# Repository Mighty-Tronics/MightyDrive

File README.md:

# MT Drive — Four-Channel PWM Pump Interface

**Certified Open Source Hardware — [OSHWA LU000003](https://certification.oshwa.org/lu000003.html)**

MT Drive is an open-hardware power interface for controlling up to four brushed DC pumps or comparable inductive DC loads from an external microcontroller.

Each channel accepts an independent PWM command and switches the load through a protected low-side MOSFET stage. The microcontroller, firmware, regulated +5 V logic supply, motor supply and pumps remain external to the board.

> **Hardware status:** prototype revision V2.0, manufactured by JLCPCB and under qualification.  
> **Published electrical rating:** 2 A continuous per channel, 8 A continuous total.  
> **Extended operation:** up to 3 A per channel may be characterized, but is not guaranteed for this hardware revision.

## Main specifications

| Characteristic | Published specification |
| --- | --- |
| Number of channels | 4 independent outputs |
| Motor supply | 5–36 V DC, externally supplied |
| Continuous current | 2 A maximum per channel |
| Aggregate continuous current | 8 A maximum |
| Extended characterization | Up to 3 A per channel / 12 A total, not guaranteed |
| PWM frequency | 31.5 kHz nominal |
| PWM input levels | 3.3 V or 5 V logic |
| Logic supply | Regulated +5 V external supply |
| Switching topology | N-channel MOSFET, low-side switching |
| Intended ambient range | −10 °C to +50 °C |
| Galvanic isolation | None; logic and motor power use a common ground |
| Hardware reference | Pump Interface schematic V2.0, dated 24 April 2026 |

At 36 V and the published current rating, the board can deliver up to 72 W per load and 288 W to four loads. These values are load power, not PCB dissipation.

## Functional operation

### Power entry

The motor supply enters through `J1`:

- `PWR`: positive motor supply, 5–36 V DC;
- `GND`: common power and logic reference.

The common input stage includes:

- `D5` 15SQ100 series Schottky diode for reverse-polarity protection;
- `D6` 1.5KE43A TVS diode for supply transient suppression;
- `C1` 1000 µF, `C2` 10 µF and `C3` 100 nF for rail decoupling;
- `TP1` and `TP2` for protected `Vin+` and ground measurements.

### PWM command path

Each PWM input passes through a 1 kΩ series resistor and a 100 kΩ pull-down before entering one section of the `74AHCT125` buffer. The buffer is powered from +5 V and adapts a 3.3 V or 5 V controller signal to the 5 V MOSFET gate-control network.

The `74AHCT125` has been bench-tested for this level-adaptation function. It carries gate-drive current only and does not determine the motor-current rating.

The four buffer outputs are permanently enabled because their active-low `/OE` inputs are tied to ground. Gate pull-down resistors keep the MOSFETs off when the controller is disconnected or its outputs are high-impedance.

### Load switching

When a PWM command is high, the corresponding `IRLZ44N` MOSFET turns on. Current flows from `Vin+`, through the channel PTC, through the external load connected between `Mx+` and `Mx−`, and through the MOSFET to ground.

When the MOSFET turns off, the channel flyback diode maintains a local path for the inductive load current. A 22 Ω + 1 nF series RC snubber damps high-frequency ringing across each motor output.

## Connections

### J2 — Logic and PWM

| Pin | Signal | Description |
| ---: | --- | --- |
| 1 | +5 V | External regulated logic supply |
| 2 | GND | Common controller and power-stage reference |
| 3 | PWM1 | Channel 1 command |
| 4 | PWM2 | Channel 2 command |
| 5 | PWM3 | Channel 3 command |
| 6 | PWM4 | Channel 4 command |

### J3 — Pump outputs

| Pin | Signal | Pin | Signal |
| ---: | --- | ---: | --- |
| 1 | M3+ | 2 | M3− |
| 3 | M4+ | 4 | M4− |
| 5 | M2+ | 6 | M2− |
| 7 | M1+ | 8 | M1− |

### Test points

| Test point | Signal |
| --- | --- |
| TP1 | Protected motor rail `Vin+` |
| TP2 | GND |
| TP3 | Channel 1 gate, `Qg1` |
| TP10 | Channel 2 gate, `Qg2` |
| TP11 | Channel 3 gate, `Qg3` |
| TP12 | Channel 4 gate, `Qg4` |

## Protection and reliability architecture

Each channel contains:

- one `MF-R500` resettable PTC in the positive load feed;
- one `15SQ100` flyback diode;
- local 22 µF + 100 nF supply decoupling;
- one 22 Ω / 0.5 W + 1 nF series RC snubber;
- a 10 kΩ MOSFET gate pull-down;
- a 1N4148 gate clamp and gate-conditioning capacitors.

The protections have different roles and do not replace one another. The PTC limits sustained fault energy but is not a precision current limiter. The flyback diode controls inductive current, the snubber damps local ringing, and the TVS limits disturbances reaching the common supply rail.

The 55 V `IRLZ44N` has 19 V of absolute drain-voltage headroom at a 36 V supply. The internal qualification target is a repetitive `VDS` peak no greater than 45 V under the published load, worst switching condition and longest intended motor cable.

## Current and thermal basis

The 2 A/channel rating is based on the complete current path rather than on the headline rating of a single semiconductor.

- Four channels at 2 A give an 8 A continuous common-path current.
- Using the 15SQ100 maximum forward-voltage screening value of 0.82 V gives a conservative `D5` loss bound of 6.56 W at 8 A. Actual forward drop and case temperature must be measured.
- The `MF-R500` hold current falls with ambient temperature; 2 A retains useful margin up to the declared +50 °C design ambient.
- MOSFET conduction and switching losses are verified at 31.5 kHz from measured gate and drain waveforms.
- Power-component case temperatures are checked against the 90 °C internal qualification target.

Operation above 2 A per channel, up to 3 A, is an engineering-characterization region only. It depends on duty cycle, pump start and stall current, ambient temperature, airflow, wiring, connector losses and simultaneous channel loading.

## Integration requirements

1. Connect the controller ground to `J2 GND` before applying PWM signals.
2. Apply a regulated +5 V supply to `J2`; the board does not generate this voltage.
3. Use a current-limited motor supply for first power-up.
4. Size the supply, connectors and cable loop for 8 A continuous total current plus pump start-current transients.
5. Keep PWM and ground wiring short and route motor cables away from sensitive logic wiring.
6. Do not exceed 2 A continuous on any channel or 8 A continuous in total within the published specification.
7. Verify each pump's start and stall current before qualification in the final system.

The board does not regulate motor voltage, provide active electronic current limiting or provide galvanic isolation. It is a component for integration, not a complete protected end product.

## Validation plan

The production-representative board is verified using the following sequence:

1. Inspect component orientation, solder joints and unpowered resistance paths.
2. Apply logic power only and verify all four PWM inputs, buffer outputs and MOSFET gates at 3.3 V and 5 V input levels.
3. Test each channel with a current-limited resistive load before connecting pumps.
4. Verify operation at 31.5 kHz and 10%, 50% and 90% duty cycle.
5. Qualify one channel at 36 V / 2 A over the full duty-cycle range.
6. Qualify four simultaneous channels at 36 V / 2 A per channel after thermal stabilization.
7. Measure MOSFET `VDS` peaks and ringing with the longest intended cable.
8. Record start, stall, reverse-polarity, endurance and high-ambient behaviour.
9. Characterize operation progressively above 2 A and up to 3 A separately, without changing the published rating.
10. Complete EMC pre-compliance tests using the final PCB, pumps, supply and cabling.

No CE conformity claim is made solely from this prototype or this repository. Regulatory assessment applies to the final integrated product and its intended use.

## Repository contents

The repository separates editable design sources from documentation and generated manufacturing outputs:

| Location | Contents |
| --- | --- |
| `Documentation/` | BOM in ODS and CSV formats; schematic images; drill maps; Gerber and Excellon manufacturing files in a ZIP archive; Master Drawing; functional and engineering notes. |
| `Kicad_Files/` | Native KiCad files for viewing and editing the schematic and PCB. |
| `README.md` | Project overview, specifications, integration guidance and certification information. |
| `LICENSE.md` | Project licence information. |

The native KiCad files are the authoritative editable design sources. Rendered schematics, PDFs and manufacturing files are provided for convenient review and production, but do not replace the native source files.

Every hardware release must identify its PCB revision or release date and match it to an immutable repository tag, BOM, schematic, layout and validation evidence.

[Master Drawing — Pump Interface, Rev A](https://github.com/Mighty-Tronics/MightyDrive/blob/main/Documentation/Pump_Interface_MasterDrawing_Rev_A.pdf)

## OSHWA certification

**MT Drive is certified open source hardware under the Open Source Hardware Association (OSHWA) certification program.** The project is registered as **Mighty Drive** in the official OSHWA directory.

| Certification information | Details |
| --- | --- |
| Registered project name | Mighty Drive |
| Unique identifier (UID) | **LU000003** |
| Certification date | **3 October 2026** |
| Official registration | [OSHWA project record — LU000003](https://certification.oshwa.org/lu000003.html) |

OSHWA certification identifies projects that comply with the [Open Source Hardware Definition](https://oshwa.org/definition/). The editable design files and project documentation are published so that users can study, modify, build and distribute the design under the applicable licence.

**Certification scope:** OSHWA certification concerns open-source hardware compliance. It does not certify electrical performance, product safety or CE/EMC conformity. Hardware qualification and final-system regulatory assessment are addressed separately in the validation plan above.

The certification mark and UID refer to the project covered by the official registration. Use of the mark follows the [OSHWA Certification Mark Usage Guidelines](https://certification.oshwa.org/mark-usage.html).

## License

The hardware design and original project documentation are released under the **CERN Open Hardware Licence Version 2 — Strongly Reciprocal (`CERN-OHL-S-2.0`)**. See [`LICENSE.md`](LICENSE.md) and the [official CERN-OHL-S v2 licence text](https://ohwr.org/cern_ohl_s_v2.txt) for the applicable terms.

| Project material | License |
| --- | --- |
| Hardware design, schematic, PCB, fabrication files and BOM | CERN-OHL-S-2.0 |
| Original project documentation | CERN-OHL-S-2.0 |
| Software or firmware | None included in this release |

Third-party data sheets and manufacturer files retain their owners' respective rights and are not relicensed by their inclusion or citation. The OSHWA certification mark remains subject to OSHWA's own usage terms.

## Documentation

The detailed functional description, engineering calculations, component-level implementation and qualification criteria are provided in the project documentation under [`Documentation/`](Documentation/).

## Maintainer

[info@mightytronics.eu](mailto:info@mightytronics.eu)

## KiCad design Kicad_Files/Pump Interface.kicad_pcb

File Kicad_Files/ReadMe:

This folder include all schematics and pcb files done by Kicad 10.

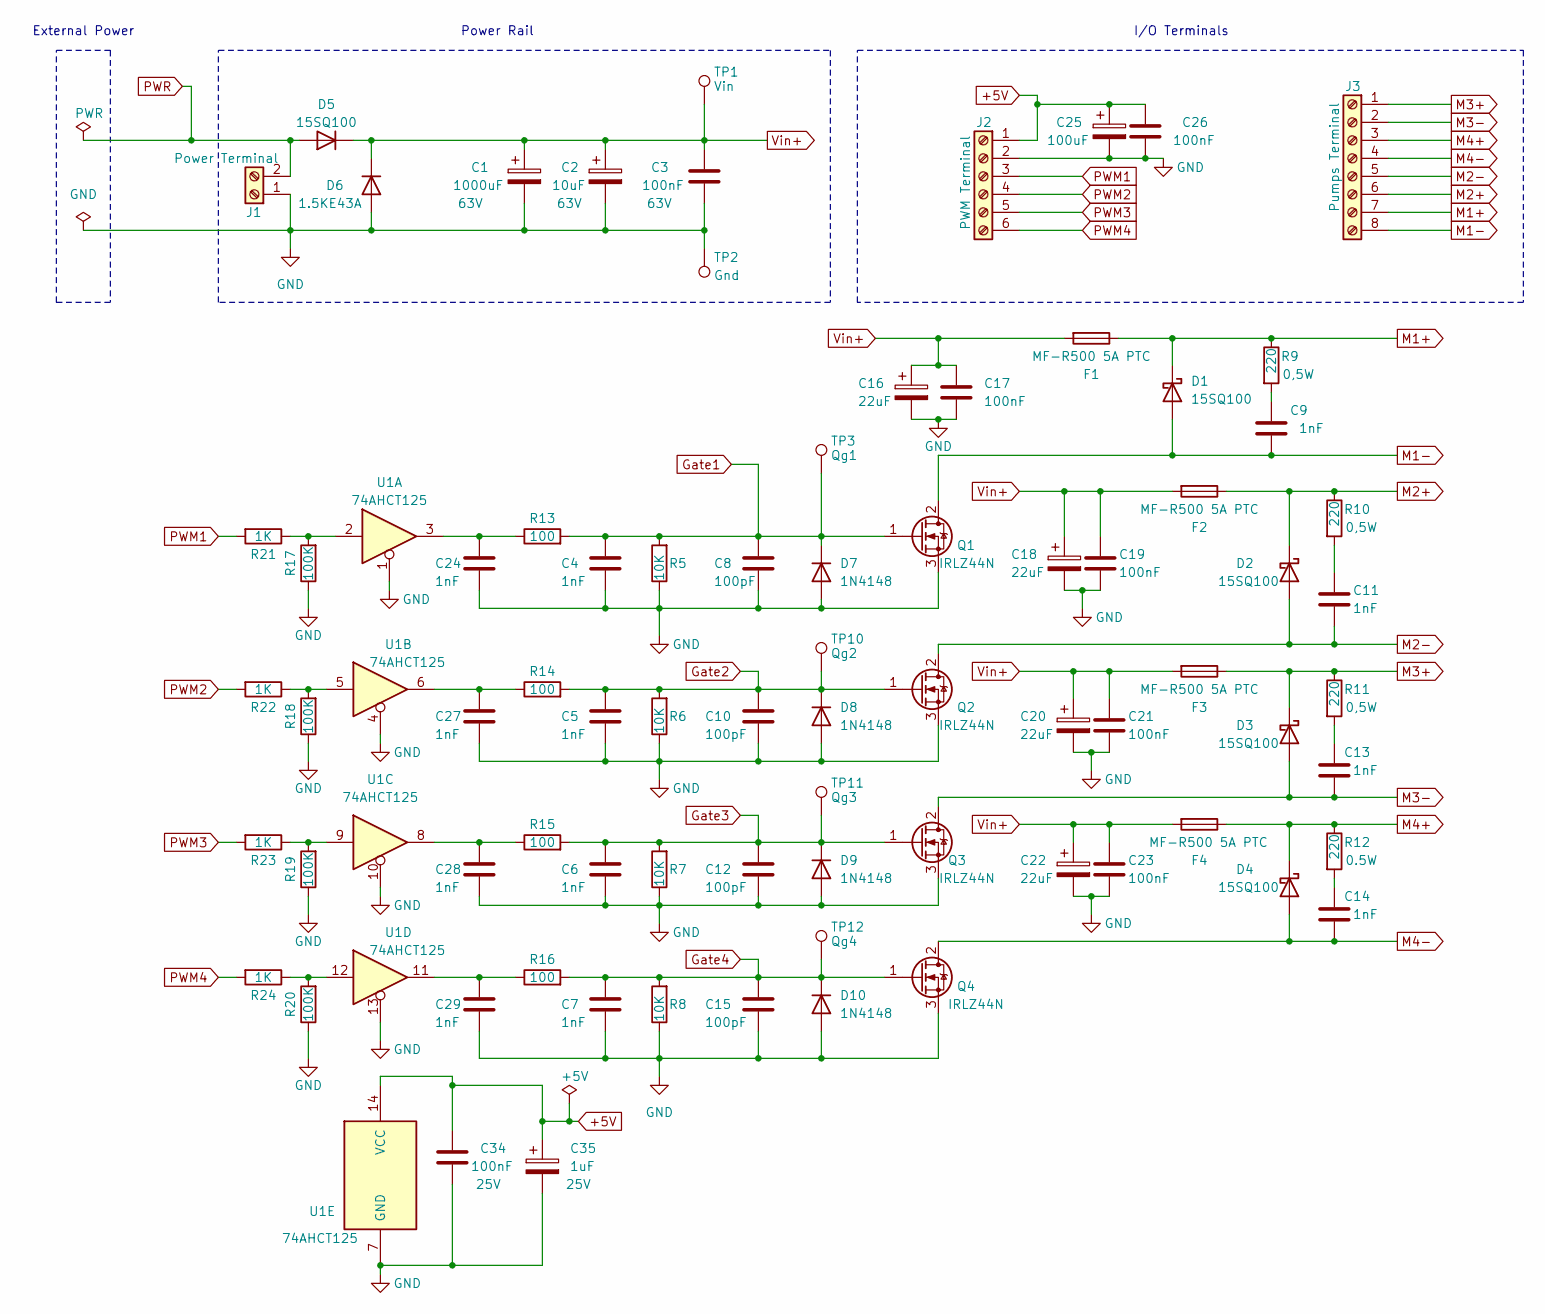
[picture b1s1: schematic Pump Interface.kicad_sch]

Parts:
C1: 1000uF; CP_Radial_D12.5mm_P5.00mm
C2: 10uF; CP_Radial_D6.3mm_P2.50mm
C3, C17, C19, C21, C23, C26: 100nF; C_Disc_D5.0mm_W2.5mm_P5.00mm
C4, C5, C6, C7, C24, C27, C28, C29: 1nF; C_Disc_D5.0mm_W2.5mm_P5.00mm
C8, C10, C12, C15: 100pF; C_Disc_D3.4mm_W2.1mm_P2.50mm
C9, C11, C13, C14: 1nF; C_Rect_L7.2mm_W2.5mm_P5.00mm_FKS2_FKP2_MKS2_MKP2
C16, C18, C20, C22: 22uF; CP_Radial_D6.3mm_P2.50mm
C25: 100uF; CP_Radial_D6.3mm_P2.50mm
C34: 100nF; C_0805_2012Metric
C35: 1uF; C_0805_2012Metric
D1, D2, D3, D4, D5: 15SQ100; D_DO-201AD_P15.24mm_Horizontal
D6: 1.5KE43A; D_DO-201AD_P15.24mm_Horizontal
D7, D8, D9, D10: 1N4148; D_DO-35_SOD27_P7.62mm_Horizontal
F1, F2, F3, F4: MF-R500 5A PTC; Fuse_Littelfuse-LVR100
J1: Power Terminal; TerminalBlock_Phoenix_MKDS-1,5-2-5.08_1x02_P5.08mm_Horizont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
J2: PWM Terminal; TerminalBlock_WAGO_233-506_2x06_P2.54mm
J3: Pumps Terminal; TerminalBlock_Phoenix_MKDS-1,5-8-5.08_1x08_P5.08mm_Horizont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
Q1, Q2, Q3, Q4: IRLZ44N; TO-220-3_Vertical
R5, R6, R7, R8: 10K; R_Axial_DIN0207_L6.3mm_D2.5mm_P10.16mm_Horizontal
R9, R10, R11, R12: 220; R_Axial_DIN0411_L9.9mm_D3.6mm_P12.70mm_Horizontal
R13, R14, R15, R16: 100; R_Axial_DIN0207_L6.3mm_D2.5mm_P10.16mm_Horizontal
R17, R18, R19, R20: 100K; R_Axial_DIN0207_L6.3mm_D2.5mm_P10.16mm_Horizontal
R21, R22, R23, R24: 1K; R_Axial_DIN0207_L6.3mm_D2.5mm_P10.16mm_Horizontal
TP1: Vin; TestPoint_Pad_1.5x1.5mm
TP2: Gnd; TestPoint_Pad_1.5x1.5mm
TP3: Qg1; TestPoint_Pad_1.5x1.5mm
TP10: Qg2; TestPoint_Pad_1.5x1.5mm
TP11: Qg3; TestPoint_Pad_1.5x1.5mm
TP12: Qg4; TestPoint_Pad_1.5x1.5mm
U1: 74AHCT125; SOIC-14_3.9x8.7mm_P1.27mm

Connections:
+5V: C25.1, C26.2, C34.2, C35.1, J2.1, U1.14 (VCC)
GND: C1.2, C2.2, C3.1, C4.1, C5.1, C6.1, C7.1, C8.1, C10.1, C12.1, C15.1, C16.2, C17.2, C18.2, C19.2, C20.2, C21.2, C22.2, C23.2, C24.1, C25.2, C26.1, C27.1, C28.1, C29.1, C34.1, C35.2, D6.2 (A), D7.2 (A), D8.2 (A), D9.2 (A), D10.2 (A), J1.1, J2.2, Q1.3 (S), Q2.3 (S), Q3.3 (S), Q4.3 (S), R5.1, R6.1, R7.1, R8.1, R17.1, R18.1, R19.1, R20.1, TP2.1 (1_1), U1.1, U1.4, U1.7 (GND), U1.10, U1.13
Gate1: C4.2, C8.2, D7.1 (K), Q1.1 (G), R5.2, R13.2, TP3.1 (1_1)
Gate2: C5.2, C10.2, D8.1 (K), Q2.1 (G), R6.2, R14.2, TP10.1 (1_1)
Gate3: C6.2, C12.2, D9.1 (K), Q3.1 (G), R7.2, R15.2, TP11.1 (1_1)
Gate4: C7.2, C15.2, D10.1 (K), Q4.1 (G), R8.2, R16.2, TP12.1 (1_1)
M1+: D1.1 (K), F1.1, J3.7, R9.1
M1-: C9.2, D1.2 (A), J3.8, Q1.2 (D)
M2+: D2.1 (K), F2.1, J3.6, R10.1
M2-: C11.2, D2.2 (A), J3.5, Q2.2 (D)
M3+: D3.1 (K), F3.1, J3.1, R11.1
M3-: C13.2, D3.2 (A), J3.2, Q3.2 (D)
M4+: D4.1 (K), F4.1, J3.3, R12.1
M4-: C14.2, D4.2 (A), J3.4, Q4.2 (D)
unnamed: C9.1, R9.2
unnamed: C11.1, R10.2
unnamed: C13.1, R11.2
unnamed: C14.1, R12.2
unnamed: C24.2, R13.1, U1.3
unnamed: C27.2, R14.1, U1.6
unnamed: C28.2, R15.1, U1.8
unnamed: C29.2, R16.1, U1.11
unnamed: R17.2, R21.1, U1.2
unnamed: R18.2, R22.1, U1.5
unnamed: R19.2, R23.1, U1.9
unnamed: R20.2, R24.1, U1.12
PWM1: J2.3, R21.2
PWM2: J2.4, R22.2
PWM3: J2.5, R23.2
PWM4: J2.6, R24.2
PWR: D5.2 (A), J1.2
Vin+: C1.1, C2.1, C3.2, C16.1, C17.1, C18.1, C19.1, C20.1, C21.1, C22.1, C23.1, D5.1 (K), D6.1 (K), F1.2, F2.2, F3.2, F4.2, TP1.1 (1_1)

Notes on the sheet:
I/O Terminals
External Power
Power Rail

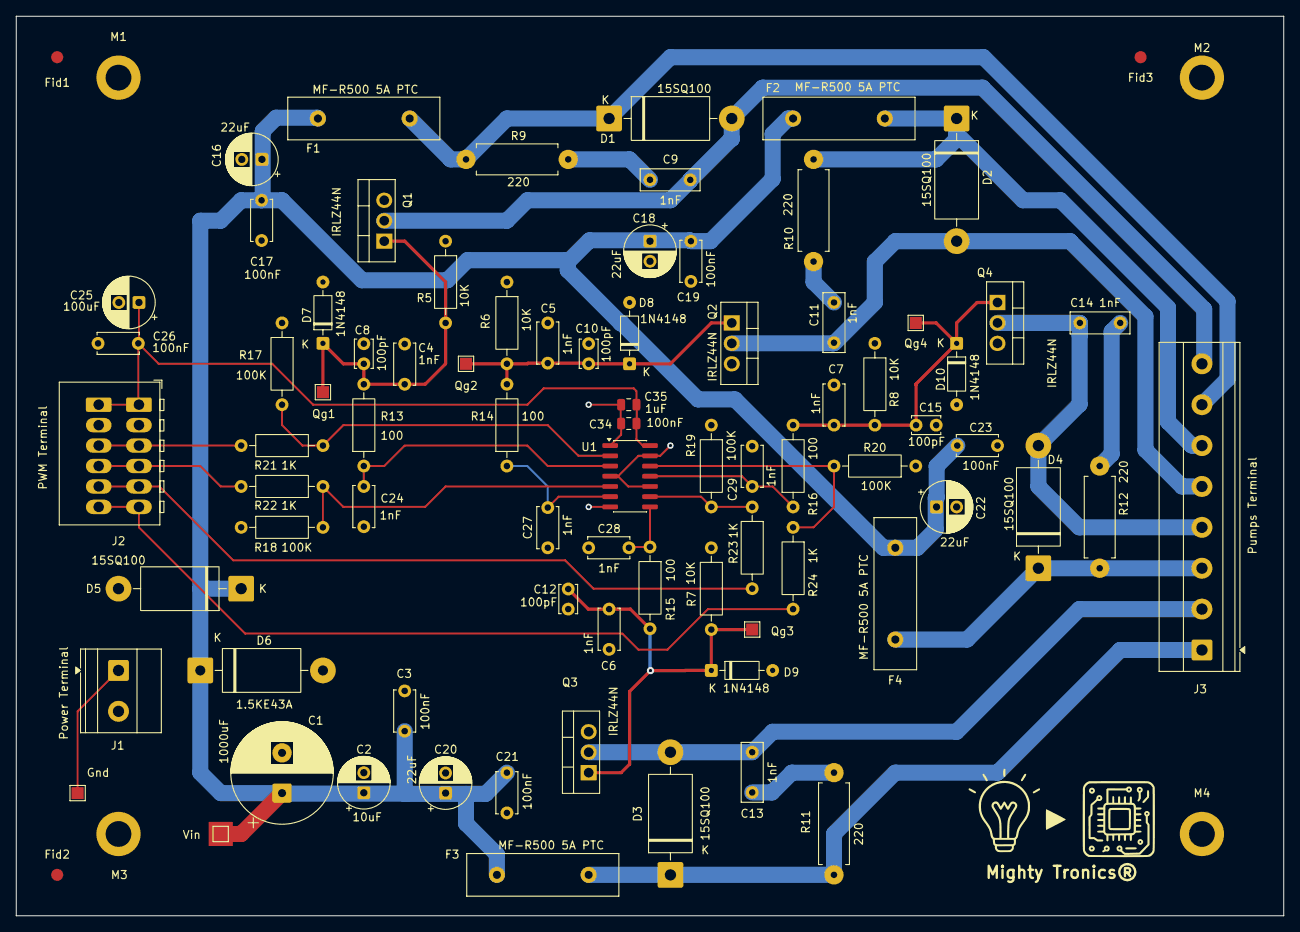
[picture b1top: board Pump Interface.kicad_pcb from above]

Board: 4 copper layers, 157.5 x 111.8 mm, 87 parts (0 on the bottom side), 32 nets.

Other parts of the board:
Fid1, Fid2, Fid3: Fiducial_1.5mm_Mask3mm
M1, M2, M3, M4: MountingHole_3.2mm_M3_ISO14580_Pad
Mighty Tronics®: LOGO; Logo-MT-PCB

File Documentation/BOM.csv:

,,,,,,,,,,,,,,
"MTDrive  bill of materials, schematic V2.0",,,,,,,,,,,,,,
"All components THT except U1, C34 and C35. Suggested footprints require PCB confirmation.",,,,,,,,,,,,,,
,,,,,,,,,,,,,,
References,Qty,Value,Function / location,Technology / specification,Mount,Package / footprint to confirm,Voltage rating (V),Power rating (W),Manufacturer P/N,Supplier P/N,Status / engineering check,,Review priorities,
C1,1,1000 uF,Main DC bus,"Aluminium electrolytic, ripple/ESR specified",THT,Radial; size and pitch TBD,100,,,,Existing 63 V marking to revise; verify surge and physical fit,,D5,Thermal dissipation in 12 A common input
C2,1,10 uF,Main DC bus,Aluminium electrolytic,THT,Radial; size and pitch TBD,100,,,,Existing 63 V marking to revise,,R9-R12,220 ohm in supplied schematic; confirm actual build
C3,1,100 nF,Main DC bus,Ceramic X7R; effective capacitance at 36 V,THT,Radial disc; pitch TBD,100,,,,Existing 63 V marking to revise,,U1,74AHCT125 versus 74HCT125 identification
C4-C7,4,1 nF,Gate network,Ceramic C0G/NP0,THT,Radial disc; pitch TBD,50,,,,Confirm exact gate-source voltage,,PCB,Verify all proposed footprints and motor switching nets
"C8,C10,C12,C15",4,100 pF,Gate network,Ceramic C0G/NP0,THT,Radial disc; pitch TBD,50,,,,,,,
"C9,C11,C13,C14",4,1 nF,Motor snubbers,Pulse-rated polypropylene film,THT,Radial film; pitch TBD,160,,,,160 V provisional; check measured transient and pulse rating,,,
"C16,C18,C20,C22",4,22 uF,Channel bus,Aluminium electrolytic; ripple/ESR specified,THT,Radial; size and pitch TBD,100,,,,,,,
"C17,C19,C21,C23",4,100 nF,Channel bus,Ceramic X7R; DC bias checked,THT,Radial disc; pitch TBD,100,,,,,,,
"C24,C27-C29",4,1 nF,Buffer output filter,Ceramic C0G/NP0,THT,Radial disc; pitch TBD,50,,,,Only buffer supply capacitors C34/C35 are SMD,,,
C25,1,100 uF,5 V input,Aluminium electrolytic,THT,Radial; size and pitch TBD,16,,,,,,,
C26,1,100 nF,5 V input,Ceramic X7R,THT,Radial disc; pitch TBD,25,,,,,,,
C34,1,100 nF,U1 local 5 V decoupling,Ceramic X7R,SMD,0805 candidate; verify PCB,25,,,,One of the two SMD capacitors,,,
C35,1,1 uF,U1 local 5 V decoupling,Ceramic X7R; DC bias checked,SMD,0805/1206 candidate; verify PCB,25,,,,One of the two SMD capacitors,,,
D1-D4,4,15SQ100,Per-channel freewheel diode,"Schottky, 100 V / 15 A nominal; thermal check",THT,R-6 axial; verify exact vendor,,,,,Datasheet link in screenshot points to unrelated 1N5817,,,
D5,1,15SQ100,Series input polarity diode,"Schottky, 100 V / 15 A nominal; thermal check at 12 A",THT,R-6 axial; verify exact vendor,,,,,Critical thermal review of common 12 A path,,,
D6,1,1.5KE43A,Supply TVS,Unidirectional TVS; verify polarity and surge energy,THT,DO-201 axial candidate; confirm vendor,,,,,Check clamp voltage against all bus parts,,,
D7-D10,4,1N4148,Gate clamp network,Small-signal switching diode,THT,DO-35 axial,,,,,Check orientation and forward-current pulses,,,
F1-F4,4,MF-R500 5A PTC,Per-channel resettable protection,PTC hold/trip current at operating temperature,THT,Radial PTC; pitch TBD,,,,,Verify I_hold at 50 C for 3 A and startup trip behavior,,,
J1,1,Power Terminal,Pump supply input,Terminal block; >=12 A continuous plus margin,THT,Pitch and footprint TBD,,,,,Check total current and cable gauge,,,
J2,1,PWM Terminal,Logic supply and 4 PWM inputs,Terminal block; pinout and pitch TBD,THT,Pitch and footprint TBD,,,,,,,,
J3,1,Pumps Terminal,Four motor outputs,Terminal block; >=3 A each plus margin,THT,Pitch and footprint TBD,,,,,Check each contact rating,,,
Q1-Q4,4,IRLZ44N,Four switching MOSFETs,Logic-level N-channel; hot R_DS(on)/SOA check,THT,TO-220-3; verify PCB orientation,,,,,Confirm pin mapping and net topology before power testing,,,
R5-R8,4,10 kohm,Gate pull-down,Resistor; tolerance TBD,THT,Axial; pitch TBD,,"0,25",,,Power rating provisional,,,
R9-R12,4,220 ohm,Snubber resistor,Pulse-rated resistor,THT,Axial; pitch TBD,,"0,5",,,"Schematic shows 220 ohm / 0.5 W, not 22 ohm; verify pulse energy",,,
R13-R16,4,100 ohm,Gate series resistor,Resistor; pulse behavior check,THT,Axial; pitch TBD,,"0,25",,,Power rating provisional,,,
R17-R20,4,100 kohm,PWM input pull-down,Resistor,THT,Axial; pitch TBD,,"0,25",,,Power rating provisional,,,
R21-R24,4,1 kohm,PWM input series resistor,Resistor,THT,Axial; pitch TBD,,"0,25",,,Power rating provisional,,,
U1,1,74AHCT125,Quad logic buffer,3.3 V compatible input at 5 V supply; exact P/N TBD,SMD,SOIC-14 candidate; verify PCB,,,,,Screenshot says 74AHCT125; verify BOM and actual IC marking,,,
